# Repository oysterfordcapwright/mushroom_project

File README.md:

# Automated Mushroom Fruiting Unit (AMFU)

A Raspberry Pi-based automated environmental control system for mushroom cultivation. This project provides precise control over temperature, humidity, CO₂ levels, and lighting to create optimal fruiting conditions for various mushroom species.

## Project Overview

The AMFU is a self-contained system that automates the fruiting stage of mushroom cultivation. It features a web-based interface for remote monitoring and control, making mushroom growing more accessible and reliable for both hobbyists and small-scale growers.

## Repository Structure

### Core Software
- **Flask Application** - Friendly web interface for system control and monitoring
- **Component Libraries** - Python drivers for all sensors and actuators:
  - Temperature and humidity sensors (DS18B20, DHT22)
  - CO₂ sensor (MH-Z19B) 
  - Lighting control (Neopixel, custom LED circuits)
  - Actuator drivers (Peltier, fans, servos, humidifier)
- **Control System** - Smart environmental management that handles parameter conflicts

### Hardware Design
- **CAD Models** - 3D printable enclosure components and mounting brackets
- **PCB Designs** - Custom Raspberry Pi hat for cleaner wiring

### Documentation
- **Component Datasheets** - Technical specifications for all hardware
- **Mushroom Results** - Yield after 1 week
- **Timelapse Examples** - Watch the mushrooms grow!

## Key Features

- **Multi-parameter control** - Temperature, humidity, CO₂, and lighting all managed automatically
- **Web-based access** - Monitor and adjust conditions from any device
- **Real-time data logging** - Watch your environmental parameters live
- **Automated time-lapse** - Capture your mushroom's growth journey
- **Contamination control** - HEPA filtration keeps chamber isolated

## Perfect For

- Home mushroom cultivation enthusiasts
- Educators teaching controlled environment agriculture
- Small-scale specialty mushroom producers
- Anyone fascinated with environmental automation

---

*Happy growing!* 🍄

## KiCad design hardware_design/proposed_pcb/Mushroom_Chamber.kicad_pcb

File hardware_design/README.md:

Contains the CAD .stl files and KiCad project files designed for the AMFU project.

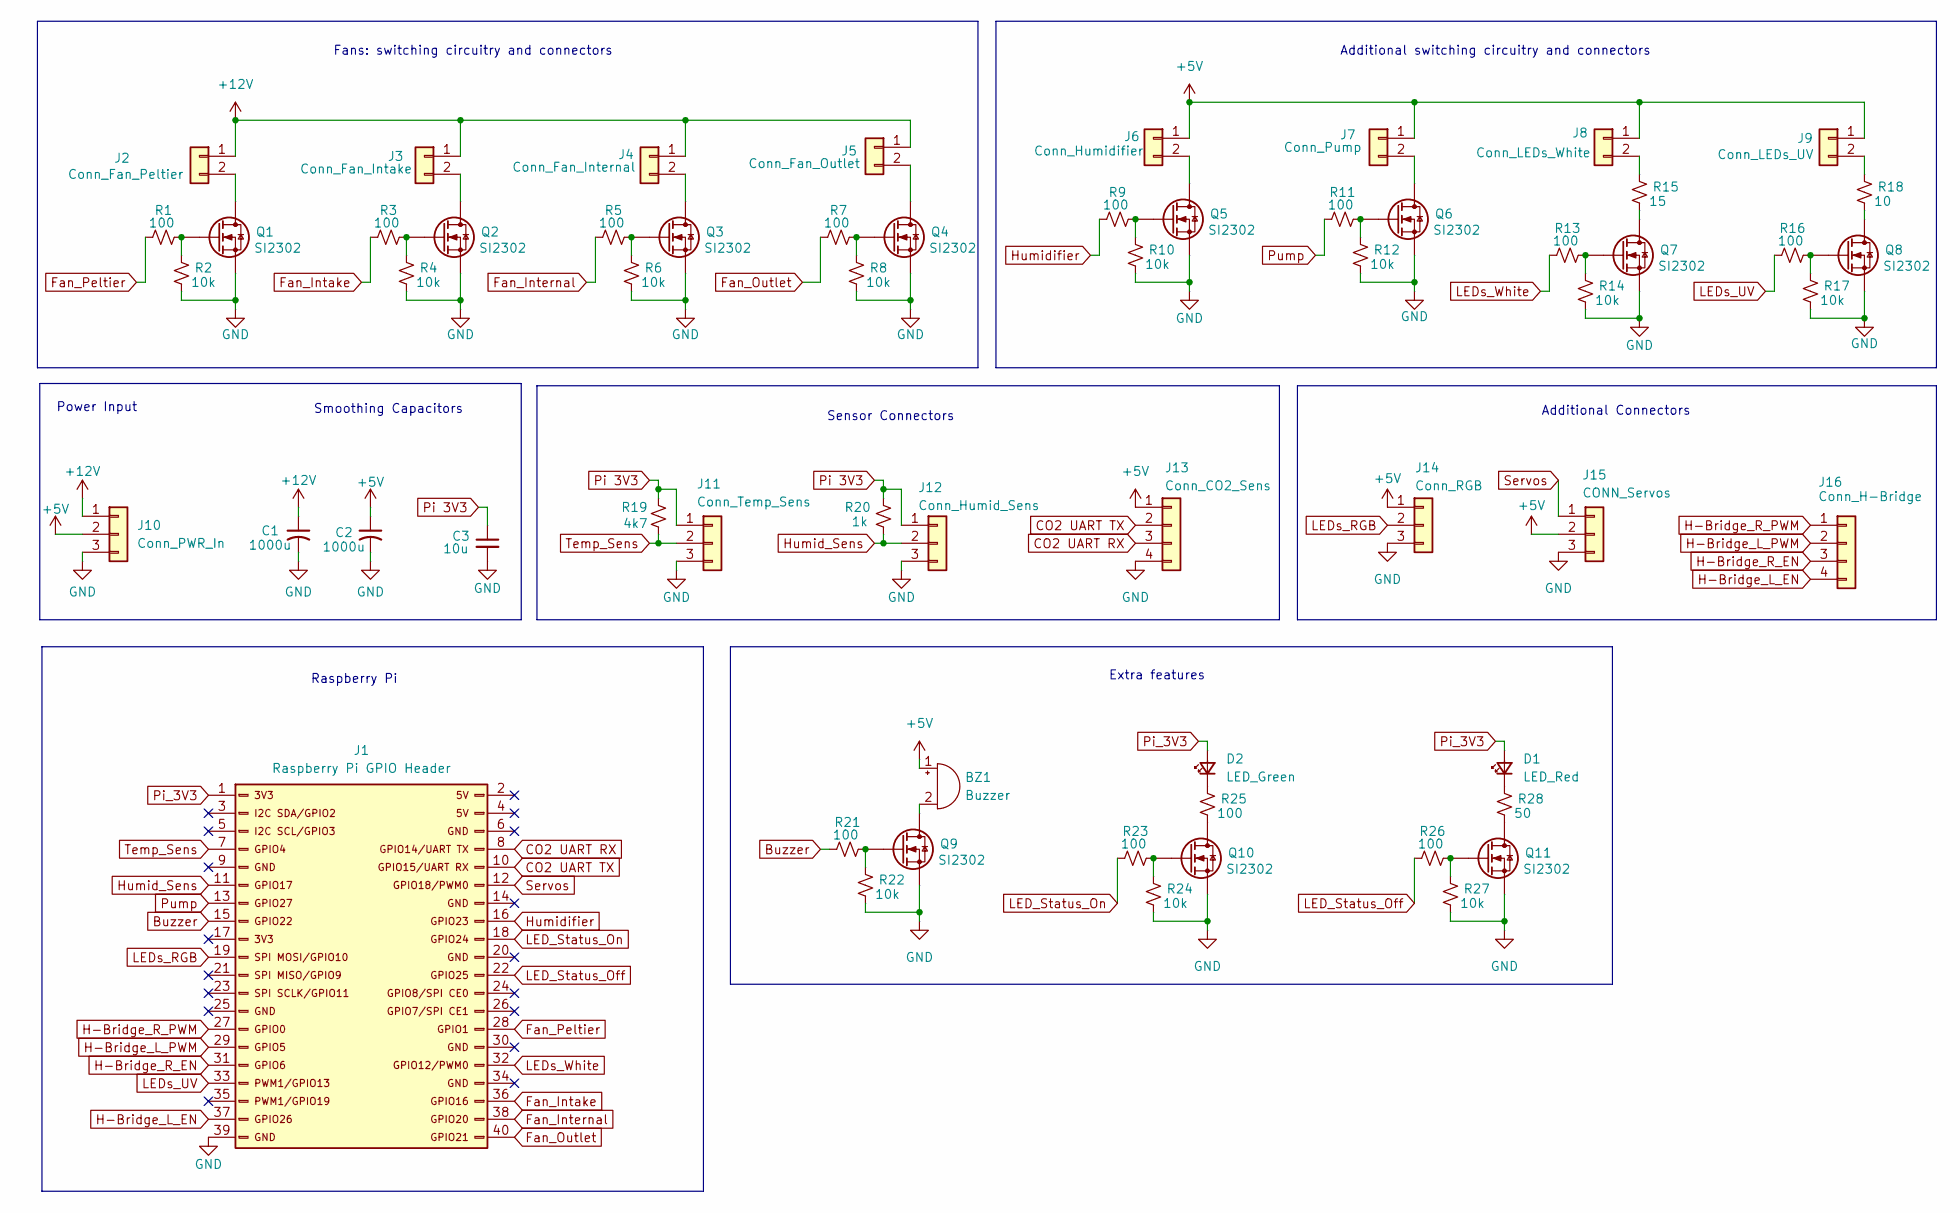
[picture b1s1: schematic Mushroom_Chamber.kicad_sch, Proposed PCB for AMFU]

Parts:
BZ1: Buzzer; BUZ-TH_BD12.0-P7.60-D0.6-FD
C1, C2: 1000u; CP_Radial_D10.0mm_P5.00mm
C3: 10u; C_0603_1608Metric
D1: LED_Red; LED_0603_1608Metric
D2: LED_Green; LED_0603_1608Metric
J1: Raspberry Pi GPIO Header; PinSocket_2x20_P2.54mm_Vertical
J2: Conn_Fan_Peltier; JST_PH_B2B-PH-K_1x02_P2.00mm_Vertical
J3: Conn_Fan_Intake; JST_PH_B2B-PH-K_1x02_P2.00mm_Vertical
J4: Conn_Fan_Internal; JST_PH_B2B-PH-K_1x02_P2.00mm_Vertical
J5: Conn_Fan_Outlet; JST_PH_B2B-PH-K_1x02_P2.00mm_Vertical
J6: Conn_Humidifier; JST_PH_B2B-PH-K_1x02_P2.00mm_Vertical
J7: Conn_Pump; JST_PH_B2B-PH-K_1x02_P2.00mm_Vertical
J8: Conn_LEDs_White; JST_PH_B2B-PH-K_1x02_P2.00mm_Vertical
J9: Conn_LEDs_UV; JST_PH_B2B-PH-K_1x02_P2.00mm_Vertical
J10: Conn_PWR_In; CONN-TH_3P-P7.62_1717732
J11: Conn_Temp_Sens; PinSocket_1x03_P2.54mm_Vertical
J12: Conn_Humid_Sens; PinSocket_1x03_P2.54mm_Vertical
J13: Conn_CO2_Sens; PinSocket_1x04_P2.54mm_Vertical
J14: Conn_RGB; JST_PH_B3B-PH-K_1x03_P2.00mm_Vertical
J15: CONN_Servos; PinSocket_1x03_P2.54mm_Vertical
J16: Conn_H-Bridge; PinSocket_1x04_P2.54mm_Vertical
Q1, Q2, Q3, Q4, Q5, Q6, Q7, Q8, Q9, Q10, Q11: SI2302; SOT-23_L2.9-W1.3-P1.90-LS2.4-BR
R1, R3, R5, R7, R9, R11, R13, R16, R21, R23, R26: 100; R_0402_1005Metric
R2, R4, R6, R8, R10, R12, R14, R17, R22, R24, R27: 10k; R_0402_1005Metric
R15: 15; RES-TH_BD6.0-L17.5-P21.50-D0.7
R18: 10; RES-TH_BD6.0-L17.5-P21.50-D0.7
R19: 4k7; R_0402_1005Metric
R20: 1k; R_0402_1005Metric
R25: 100; R_0805_2012Metric
R28: 50; R_0805_2012Metric

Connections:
+5V: BZ1.1 (+), C2.1, J6.1, J7.1, J8.1, J9.1, J10.2, J13.1, J14.1, J15.2
+12V: C1.1, J2.1, J3.1, J4.1, J5.1, J10.1
Buzzer: J1.15, R21.1
CO2 UART RX: J1.8, J13.3
CO2 UART TX: J1.10, J13.2
Fan_Intake: J1.36, R3.1
Fan_Internal: J1.38, R5.1
Fan_Outlet: J1.40, R7.1
Fan_Peltier: J1.28, R1.1
GND: C1.2, C2.2, C3.2, J1.39, J10.3, J11.3, J12.3, J13.4, J14.3, J15.3, Q1.2 (S), Q2.2 (S), Q3.2 (S), Q4.2 (S), Q5.2 (S), Q6.2 (S), Q7.2 (S), Q8.2 (S), Q9.2 (S), Q10.2 (S), Q11.2 (S), R2.2, R4.2, R6.2, R8.2, R10.2, R12.2, R14.2, R17.2, R22.2, R24.2, R27.2
H-Bridge_L_EN: J1.37, J16.4
H-Bridge_L_PWM: J1.29, J16.2
H-Bridge_R_EN: J1.31, J16.3
H-Bridge_R_PWM: J1.27, J16.1
Humid_Sens: J1.11, J12.2, R20.2
Humidifier: J1.16, R9.1
LED_Status_Off: J1.22, R26.1
LED_Status_On: J1.18, R23.1
LEDs_RGB: J1.19, J14.2
LEDs_UV: J1.33, R16.1
LEDs_White: J1.32, R13.1
unnamed: BZ1.2 (-), Q9.3 (D)
unnamed: D1.1 (K), R28.1
unnamed: D2.1 (K), R25.1
unnamed: J2.2, Q1.3 (D)
unnamed: J3.2, Q2.3 (D)
unnamed: J4.2, Q3.3 (D)
unnamed: J5.2, Q4.3 (D)
unnamed: J6.2, Q5.3 (D)
unnamed: J7.2, Q6.3 (D)
unnamed: J8.2, R15.1
unnamed: J9.2, R18.1
unnamed: Q1.1 (G), R1.2, R2.1
unnamed: Q2.1 (G), R3.2, R4.1
unnamed: Q3.1 (G), R5.2, R6.1
unnamed: Q4.1 (G), R7.2, R8.1
unnamed: Q5.1 (G), R9.2, R10.1
unnamed: Q6.1 (G), R11.2, R12.1
unnamed: Q7.3 (D), R15.2
unnamed: Q7.1 (G), R13.2, R14.1
unnamed: Q8.3 (D), R18.2
unnamed: Q8.1 (G), R16.2, R17.1
unnamed: Q9.1 (G), R21.2, R22.1
unnamed: Q10.3 (D), R25.2
unnamed: Q10.1 (G), R23.2, R24.1
unnamed: Q11.3 (D), R28.2
unnamed: Q11.1 (G), R26.2, R27.1
Pi 3V3: C3.1, J11.1, J12.1, R19.1, R20.1
Pi_3V3: D1.2 (A), D2.2 (A), J1.1
Pump: J1.13, R11.1
Servos: J1.12, J15.1
Temp_Sens: J1.7, J11.2, R19.2

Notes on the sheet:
Sensor Connectors
Extra features
Power Input
Fans: switching circuitry and connectors
Raspberry Pi
Additional switching circuitry and connectors
Additional Connectors
Smoothing Capacitors

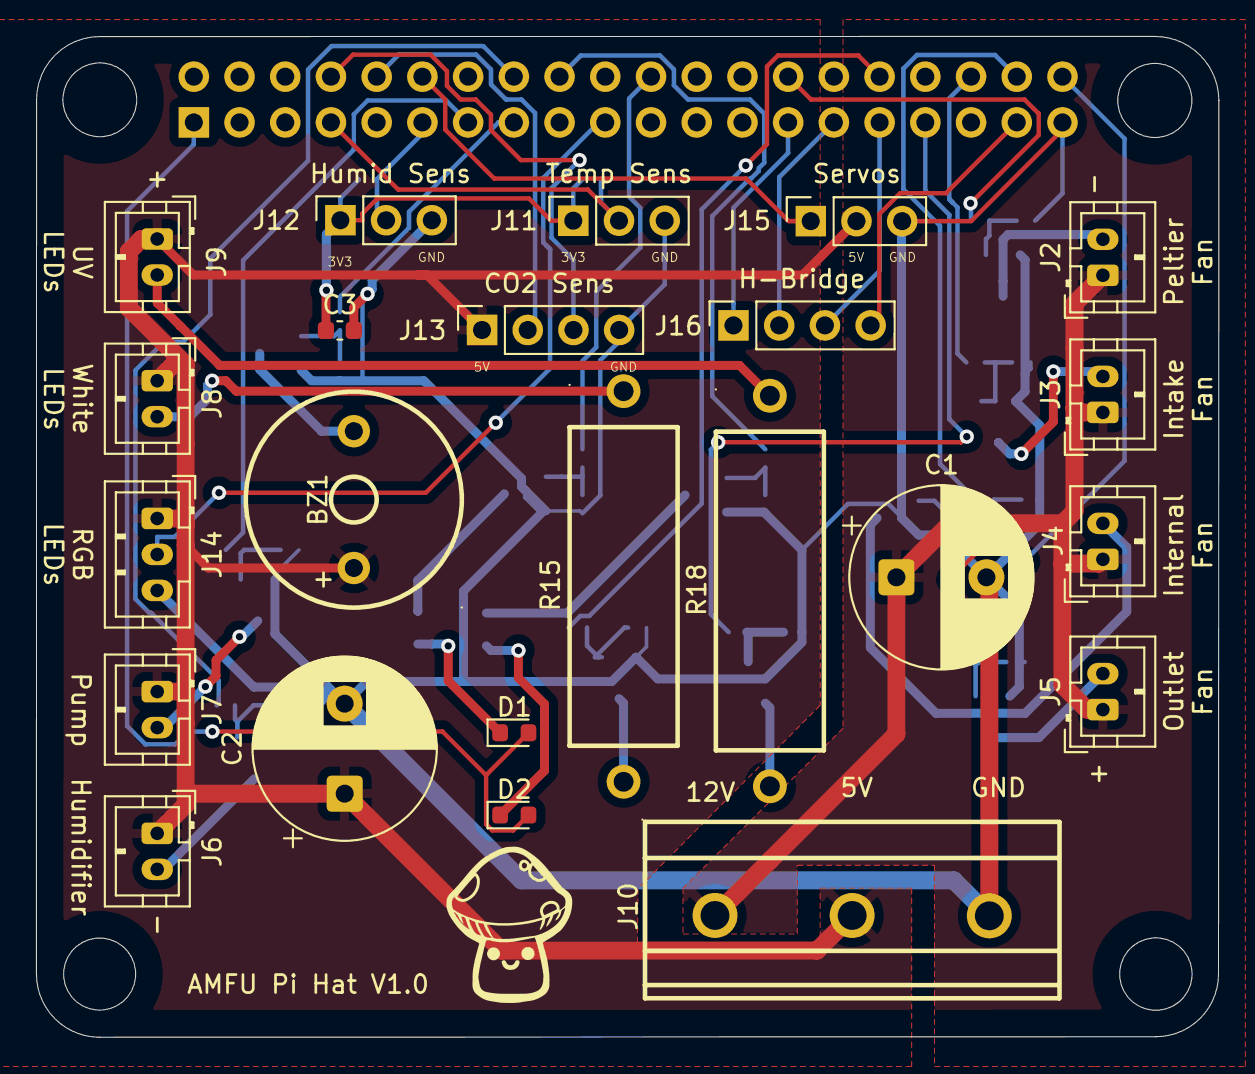
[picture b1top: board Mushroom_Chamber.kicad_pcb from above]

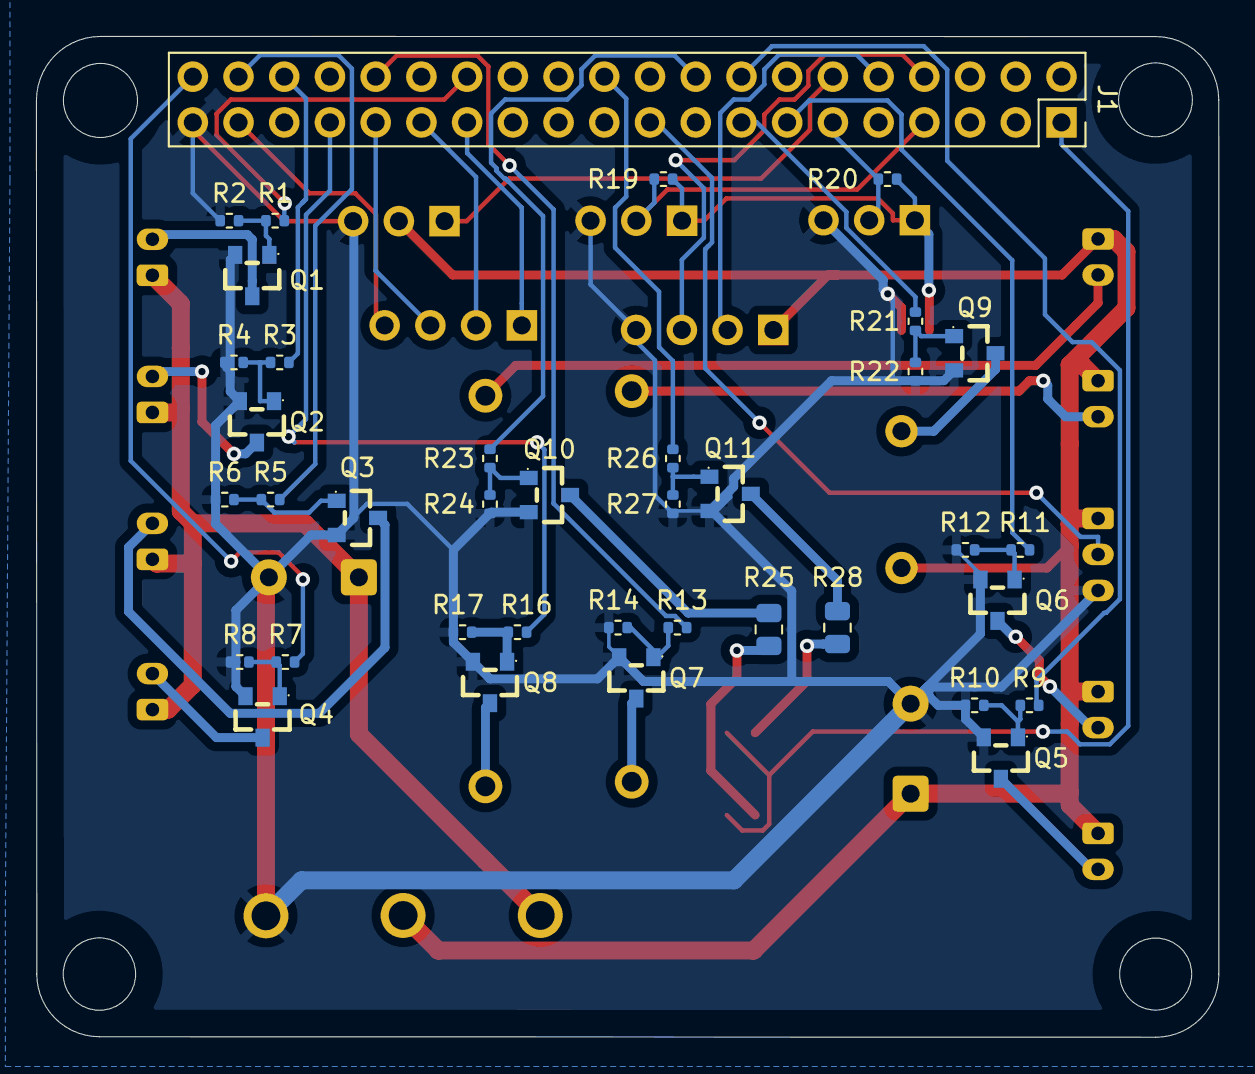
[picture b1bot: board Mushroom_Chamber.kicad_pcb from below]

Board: 2 copper layers, 65.7 x 55.6 mm, 61 parts (38 on the bottom side), 52 nets.

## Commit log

2025-09-01 Changed Camera file name, add temperature monitor
2025-09-01 added colour to text boxes, added peltier file, timelapse interval adjustment working
2025-10-03 Added servo library, added device controller lib
2025-10-03 Completed device controller library up to neos
2025-10-05 Control program basics working
2025-10-13 Working Mostly
2025-10-15 UPdating PID
2025-10-15 Updated PIDs
2025-10-28 Added mushroom growth timelapse and gif
2025-10-28 Rename Mushroom growth.gif to mushroom_growth.gif
2025-10-28 Update READM gif
2025-10-28 Create 3d_cad_models
2025-10-28 Updated comments
